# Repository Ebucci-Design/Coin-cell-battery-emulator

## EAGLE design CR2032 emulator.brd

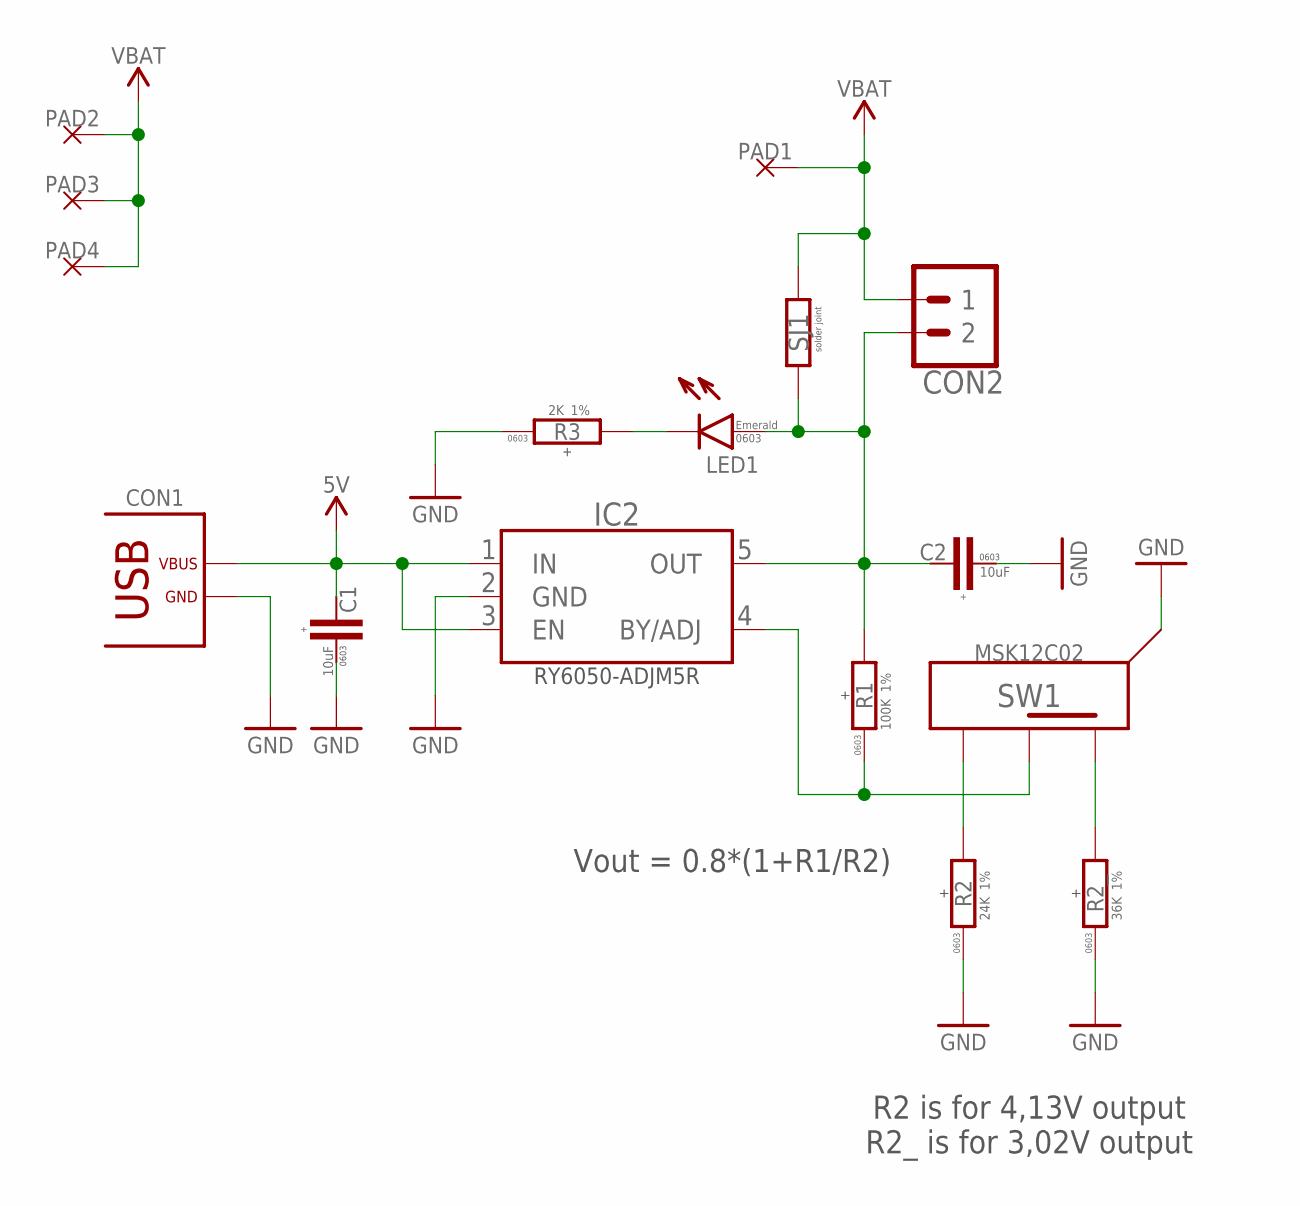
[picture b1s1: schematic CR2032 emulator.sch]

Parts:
C1, C2: 10uF; C0603; LCSC# C96446
CON1: USB_PWR-31-M-17; TYPEC31M17
CON2: PINHEAD_1X02-2; 1X02-PTH-2
IC2: RY6050-ADJM5R; SOT23-5
LED1: LED-0603; LED0603; LCSC# C72043
PAD1: PAD-3X1.5; 3X1.5
PAD2, PAD3, PAD4: PAD-HOLE-0.6; HOLE_0.6
R1: 100K; R0603; LCSC# C25803
R2: 24K; R0603; LCSC# C23352
R2_: 36K; R0603; LCSC# C23147
R3: 2K; R0603; LCSC# C22975
SJ1: SOLDER_JOINT-SJ2; SOLDER_JOINT_SMALL
SW1: SPDT_SWITCH; MSK-12C02

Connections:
GND: C1.1, C2.1, CON1.A12 (GND), CON1.B12 (GND), IC2.2 (GND), R2.1, R2_.1, R3.1, SW1.GND@1 (PADS), SW1.GND@2 (PADS), SW1.GND@3 (PADS), SW1.GND@4 (PADS)
unnamed: LED1.C, R3.2
unnamed: C2.2, CON2.2, IC2.5 (OUT), LED1.A, R1.2, SJ1.1
unnamed: R2_.2, SW1.L1 (NC)
unnamed: R2.2, SW1.L2 (NO)
unnamed: IC2.4 (BY/ADJ), R1.1, SW1.COM
VBAT: CON2.1, PAD1.P$1, PAD2.P$1, PAD3.P$1, PAD4.P$1, SJ1.2
VDD_5V: C1.2, CON1.A9 (VBUS), CON1.B9 (VBUS), IC2.1 (IN), IC2.3 (EN)

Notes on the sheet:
Vout = 0.8*(1+R1/R2)
R2 is for 4,13V output R2_ is for 3,02V output

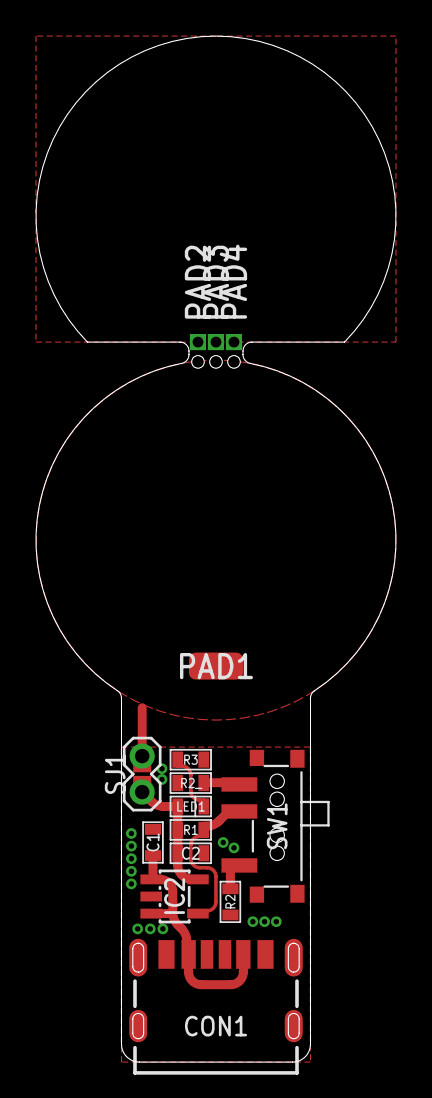
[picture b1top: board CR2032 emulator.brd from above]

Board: 2 copper layers, 20.0 x 57.0 mm, 16 parts (0 on the bottom side), 8 nets.

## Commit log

2022-04-07 initial import
2022-04-07 attribute updates
2022-04-07 minor updates
2022-04-07 silkscreen updates
